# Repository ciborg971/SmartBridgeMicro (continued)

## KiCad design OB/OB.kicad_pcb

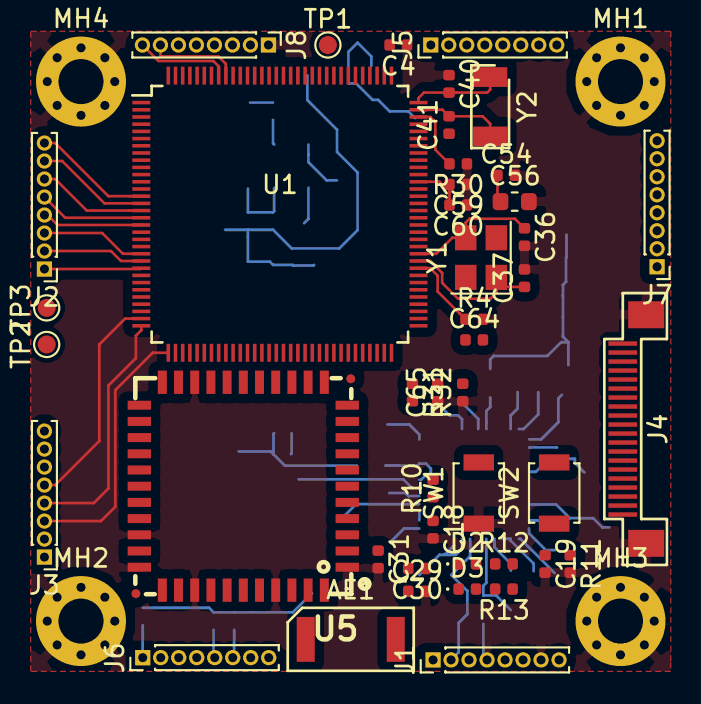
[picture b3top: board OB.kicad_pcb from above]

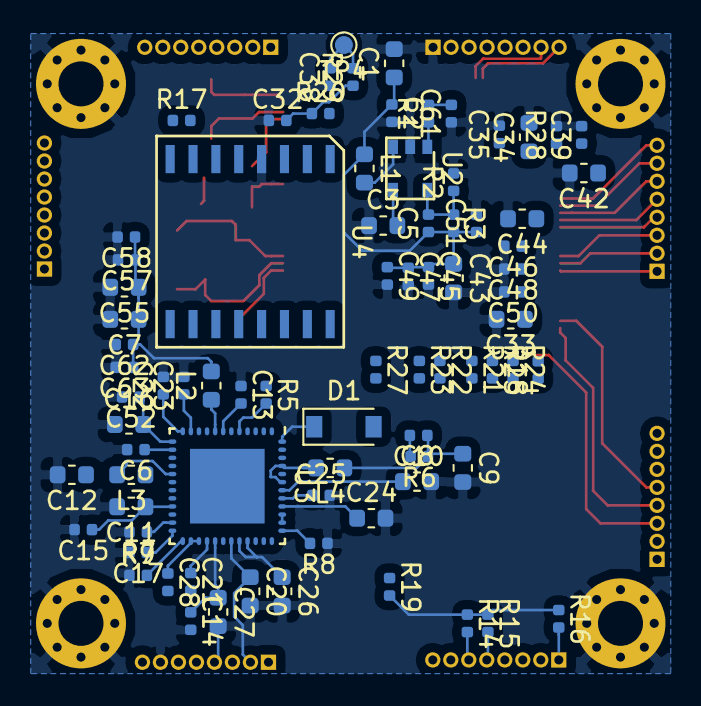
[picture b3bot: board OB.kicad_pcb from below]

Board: 2 copper layers, 128 parts (80 on the bottom side), 126 nets.

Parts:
AE1: 2.4Ant; SOIC-2
C1, C3, C7, C8, C9, C11, C12, C16, C20, C24, C26, C27, C33, C34, C42, C43, C44, C55, C56: 10uF; C_0603_1608Metric
C2, C15, C32: 104; C_0402_1005Metric
C4, C13, C14, C22, C23, C25: 4.7uF; C_0402_1005Metric
C5: 47pF; C_0402_1005Metric
C6: 10uF; C_0402_1005Metric
C10, C17, C21, C28, C29, C30, C31, C35, C38, C45, C46, C47, C52, C57, C58: 1uF; C_0402_1005Metric
C18, C19: 100pF; C_0402_1005Metric
C36, C37: 18pF; C_0402_1005Metric
C39, C48, C49, C50, C51, C54, C59, C60, C61, C62, C63, C64, C65: 104F; C_0402_1005Metric
C40, C41: 20pF; C_0402_1005Metric
D1: 1N4148W-7-F; D_SOD-123
D2, D3: LED; LED_0402_1005Metric
J1: Power; PinHeader_1x08_P1.00mm_Vertical
J2: GPIO_A; PinHeader_1x08_P1.00mm_Vertical
J3: GPIO_B; PinHeader_1x08_P1.00mm_Vertical
J4: CAM; FPC_20
J5: SDC0; PinHeader_1x08_P1.00mm_Vertical
J6: GPIO_D; PinHeader_1x08_P1.00mm_Vertical
J7: USB_ETH; PinHeader_1x08_P1.00mm_Vertical
J8: AUDIO; PinHeader_1x08_P1.00mm_Vertical
L1: 2.2uH_1.5A DCR<0.1R; L_0603_1608Metric
L2: 4.7uH DCR<0.1R 1.1A; L_0603_1608Metric
L3: 4.7uH DCR < 0.1 1.1A; L_0603_1608Metric
L4: 4.7uH DCR < 0.1R 1.1A; L_0603_1608Metric
MH1, MH2, MH3, MH4: MountingHole_Pad; MountingHole_2.5mm_Pad_Via
R1, R18, R19: 100K; R_0402_1005Metric
R2: 100K 1%; R_0402_1005Metric
R3, R7, R28: 200K 1%; R_0402_1005Metric
R4: 240R 1%; R_0402_1005Metric
R5, R17, R27: 10K; R_0402_1005Metric
R6: 30mR; R_0402_1005Metric
R8: 100R; R_0402_1005Metric
R9, R16, R29: 47K; R_0402_1005Metric
R10, R12, R13: 1K; R_0402_1005Metric
R11, R14, R15: 2K; R_0402_1005Metric
R20: 0R; R_0402_1005Metric
R21, R22, R23, R24, R25: 33K; R_0402_1005Metric
R30: 6K 1%; R_0402_1005Metric
R31, R32: 2K 1%; R_0402_1005Metric
SW1, SW2: PWR; SW_SPST_B3U-1000P
TP1: LRADC0; TestPoint_Pad_D1.0mm
TP2: PE1; TestPoint_Pad_D1.0mm
TP3: PE0; TestPoint_Pad_D1.0mm
TP4: Rst; TestPoint_Pad_D1.0mm
U1: V3S; LQFP-128_14x14mm_P0.4mm
U2: SY8088; SOIC-6
U3: AXP203; QFN-48_EP_6.1x6.1_Pitch0.45mm
U4: MX25L12835E; SOIC-16
U5: RTL8723BS(ComboModule); RL-SM02BD(RTL8723BS)
Y1: X1E0000210832; Crystal_SMD_3225-4Pin_3.2x2.5mm
Y2: CC5V-T1A 32.768KHZ +-20PPM 12.5PF; SOIC-2

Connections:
+1V2: C7.1, C55.1, C57.1, C58.1, C62.1, C63.1, L2.2, U1.19, U1.20, U1.21, U1.25, U1.26, U1.38, U1.47, U1.51, U1.56, U1.58, U1.64, U1.80, U1.88, U1.108, U1.126, U3.10
+1V8: C1.1, C2.1, C5.1, C43.1, C45.1, C47.1, C49.1, C51.1, C64.2, L1.1, R3.2, R31.2, U1.59, U1.60, U1.61, U1.62, U1.65, U1.66, U1.67, U1.68, U1.69, U1.70, U1.72, U1.79
+3.3VA: C54.1, C56.1, C61.2, R1.2, U1.76, U1.115
+3V3: C16.2, C24.1, C32.2, C33.1, C44.1, C46.1, C48.1, C50.1, C52.1, C59.2, C60.2, D1.2, J4.8, R5.1, R12.1, R14.1, R15.1, R16.1, R17.1, R18.2, R19.2, R20.1, R21.1, R22.1, R23.1, R24.1, R25.1, R27.1, R29.1, U1.50, U1.57, U1.85, U1.93, U1.104, U1.109, U1.122, U1.127, U3.13, U3.40, U4.2, U4.8, U5.9
+BATT: C8.1, C10.2, J1.6, J4.10, R6.2, U3.38, U3.39, U3.42
/All V3s input output/CSI-PWDN: J4.2, U1.13
/All V3s input output/CSI-RESET: J4.1, U1.11
/All V3s input output/CSI-SCK: J4.5, U1.9
/All V3s input output/CSI-SDA: J4.6, U1.8
/All V3s input output/CSI_1_N: J4.16, U1.82
/All V3s input output/CSI_1_P: J4.15, U1.81
/All V3s input output/CSI_2_N: J4.13, U1.84
/All V3s input output/CSI_2_P: J4.12, U1.83
/All V3s input output/CSI_CLK_N: J4.19, U1.87
/All V3s input output/CSI_CLK_P: J4.18, U1.86
/All V3s input output/CSI_MCLK: J4.3, U1.10
/All V3s input output/EPHY_RX_N: J7.5, U1.89
/All V3s input output/EPHY_RX_P: J7.6, U1.90
/All V3s input output/EPHY_TX_N: J7.7, J7.8, U1.91, U1.92
/All V3s input output/HPCOM: J8.3, U1.125
/All V3s input output/HPCOMFB: J8.2, U1.124
/All V3s input output/MININ1N: J8.4, U1.114
/All V3s input output/MININ1P: J8.5, U1.113
/All V3s input output/SDC1_CLK: U1.5, U5.17
/All V3s input output/SDC1_CMD: R21.2, U1.4, U5.16
/All V3s input output/SDC1_D0: R22.2, U1.3, U5.18
/All V3s input output/SDC1_D1: R23.2, U1.2, U5.19
/All V3s input output/SDC1_D2: R24.2, U1.1, U5.14
/All V3s input output/SDC1_D3: R25.2, U1.128, U5.15
/All V3s input output/SPI_CLK: U1.53, U4.6
/All V3s input output/SPI_CS: R20.2, U1.54, U4.1
/All V3s input output/SPI_HOLD: R17.2, U4.7
/All V3s input output/SPI_MOSI: U1.55, U4.5
/All V3s input output/UART0_RX: J5.7, U1.48
/All V3s input output/UART0_TX: J5.8, U1.49
/All V3s input output/UART2_CTS: U1.42, U5.44
/All V3s input output/UART2_RX: U1.40, U5.42
/All V3s input output/UART2_TX: U1.39, U5.43
/All V3s input output/USB_D_N: J6.7, J7.1, U1.110
/All V3s input output/USB_D_P: J6.8, J7.2, U1.111
/All V3s input output/USB_ID: J6.1, R16.2, U1.100
/All V3s input output/VRA1: C35.1, U1.117
/All V3s input output/VRA2: C34.1, R28.1, U1.118
/PMIC Power Battery/ACIN: C26.1, J1.8, U3.32, U3.33
/PMIC Power Battery/CHGLED: D3.1, U3.36
/PMIC Power Battery/EXTEN: J1.5, U3.20
/PMIC Power Battery/LDO1: C21.1, U3.28
/PMIC Power Battery/LDO2: C22.1, U3.12
/PMIC Power Battery/LDO3: C25.1, U3.41
/PMIC Power Battery/LDO4: C23.1, U3.11
/PMIC Power Battery/N_OE: C19.1, R11.1, SW2.1, U3.4
/PMIC Power Battery/PS: C3.2, C6.1, C11.1, C13.2, C14.1, C15.1, C27.1, J1.3, R13.1, SW2.2, U2.4, U3.7, U3.14, U3.21, U3.29, U3.34, U3.35, U3.44
/PMIC Power Battery/PWRON: C18.1, R10.1, U3.47
/PMIC Power Battery/RECLED: D2.1, U3.18
/PMIC Power Battery/SVREF: C64.1, C65.2, R31.1, R32.2, U1.63, U1.71
/PMIC Power Battery/USBVBUS: C20.1, J1.2, U3.31
/PMIC Power Battery/USB_DRVVBUS: J1.1, U3.6
/PMIC Power Battery/VCC_PE: U1.12, U1.29
/PMIC Power Battery/VCC_RTC: R9.1, U1.98
/PMIC Power Battery/VINT: C28.1, U3.26, U3.27
AP-WAKE-BT: R5.2, U3.5, U5.6
GND: C1.2, C2.2, C3.1, C4.1, C6.2, C7.2, C8.2, C9.2, C11.2, C12.2, C13.1, C14.2, C15.2, C16.1, C17.2, C18.2, C19.2, C20.2, C21.2, C22.2, C23.2, C24.2, C25.2, C26.2, C27.2, C28.2, C29.2, C31.2, C32.1, C33.2, C34.2, C35.2, C36.2, C37.2, C38.1, C39.2, C40.1, C41.1, C42.2, C43.2, C44.2, C45.2, C46.2, C47.2, C48.2, C49.2, C50.2, C51.2, C52.2, C54.2, C55.2, C56.2, C57.2, C58.2, C59.1, C60.1, C61.1, C62.2, C63.2, C65.1, J1.4, J1.7, J4.4, J4.11, J4.14, J4.17, J4.20, J8.1, MH1.1, MH2.1, MH3.1, MH4.1, R2.2, R4.2, R7.2, R8.1, R11.2, R28.2, R30.1, R32.1, SW1.1, U1.116, U2.2, U3.9, U3.16, U3.22, U3.46, U3.49, U4.4, U5.1, U5.20, U5.31, U5.33, U5.36, U5.41, Y1.2, Y1.4
I2C0_CLK: J6.5, R15.2, U1.45, U3.2
I2C0_SDA: J6.6, R14.2, U1.46, U3.1
unnamed: AE1.2, C29.1, C30.2
unnamed: C4.2, U1.97
unnamed: C5.2, R2.1, R3.1, U2.5
unnamed: C9.1, C10.1, L4.1, R6.1
unnamed: C12.1, L3.2, U3.17
unnamed: C17.1, U3.24
unnamed: C30.1, C31.1, U5.2
unnamed: C36.1, U1.75, Y1.3
unnamed: C37.1, U1.74, Y1.1
unnamed: C39.1, C42.1, U1.123
unnamed: C40.2, U1.96, Y2.1
unnamed: C41.2, U1.95, Y2.2
unnamed: D1.1, U3.48
unnamed: D2.2, R12.2
unnamed: D3.2, R13.2
unnamed: J2.1, U1.24
unnamed: J2.2, U1.23
unnamed: J2.3, U1.22
unnamed: J2.4, U1.18
unnamed: J2.5, U1.17
unnamed: J2.6, U1.16
unnamed: J2.7, U1.15
unnamed: J2.8, U1.14
unnamed: J3.1, U1.35
unnamed: J3.2, U1.34
unnamed: J3.3, U1.33
unnamed: J3.4, U1.32
unnamed: J3.5, U1.31
unnamed: J3.6, U1.30
unnamed: J3.7, U1.28
unnamed: J3.8, U1.27
unnamed: J5.1, U1.107
unnamed: J5.2, U1.106
unnamed: J5.3, U1.105
unnamed: J5.4, U1.103
unnamed: J5.5, U1.102
unnamed: J5.6, U1.101
unnamed: J6.2, U1.41
unnamed: J6.3, U1.43
unnamed: J6.4, U1.44
unnamed: J7.3, U1.77
unnamed: J7.4, U1.78
unnamed: J8.6, U1.119
unnamed: J8.7, U1.120
unnamed: J8.8, U1.121
unnamed: L1.2, U2.3
unnamed: L2.1, U3.8
unnamed: L3.1, U3.15
unnamed: L4.2, U3.43, U3.45
unnamed: R1.1, U2.1
unnamed: R4.1, U1.73
unnamed: R7.1, U3.23
unnamed: R8.2, U3.37
unnamed: R10.2, SW1.2
unnamed: R18.1, U5.12
unnamed: R19.1, U5.34
unnamed: R27.2, U5.22
unnamed: R30.2, U1.94
unnamed: TP1.1, U1.112
unnamed: TP2.1, U1.36
unnamed: TP3.1, U1.37
RESET: C38.2, R9.2, R29.2, TP4.1, U1.99, U3.25

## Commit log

2019-02-06 New pmic, global cleanup
2019-02-20 Progress on wifi
2019-02-20 wifi progress on antenna
2019-02-22 wifi antenna done
2019-02-23 SmartBridgeMicro Schematic done
2019-02-23 MicroPilot schematic done
2019-04-14 +esp32picod4 +fix mounting hole position -ceramic antenna +ufl -spi flash
2019-04-14 mounting hole placement fix, routing allmost done
2019-09-22 Power Supply done, audio part fixed, icm + bpm280 added
2019-09-22 Fix commit
2019-09-23 Add i2c connector from V3s, fix sd card detection and remove todos
2019-09-23 Add more footprint, pcb format done, started component placement
2019-09-24 New component placement, progress on rooting
2019-09-26 Change Max13030 and moove ESP32
2019-09-26 ICM rooted
2019-09-28 Camera routed
2019-09-28 Sdcard part routed
2019-09-29 last 4 layers version
2019-09-29 replace 3 ldo by 1, replace icm by mpu and progress on 2 layer
2019-09-29 almost everything is routed !
2019-10-20 SD card connector re routed, only power remaining
2019-10-20 Power part autorouted, replaced micro usb connector by jst sh 5 pin
2019-11-01 progress on pcb cleaning
2019-11-01 cleaner sdcard routing, bom exported (need price and url)
2019-11-01 3 ground issues fixed
2019-11-01 antenna cleanup, ground fixing almost done
2019-11-02 routing done, started filling bom
2019-11-03 length matching done for sdcard, cleaning silkscreen, todo sdio
2019-11-04 progress on fixing esp32 sdio length
2019-11-05 esp32 sdio length matching done
2019-11-05 push to prod ?
2019-11-05 fix adp322, optimize routing
2019-11-05 fix silkscreen
2019-11-06 Apply V3s design guide recommendations
2019-11-16 Move via from pad and rebuild fab files
2019-11-17 increased power track, increased version to 0.2 and re build fab files
2019-11-25 fix d1, d2 package
2019-11-25 fix component packages
2020-06-13 FPGA_ESP32 init : psram + fpga schematic
2020-06-13 FPGA_ESP32 : add header + esp32 with SDIO
2020-06-15 FPGA_ESP32 : add 2 psram ic, rf switch
2020-06-15 FPGA_ESP32 : add spi mux
2020-07-08 FPGA_ESP32 : add camera, change header position
2020-07-10 FPGA_ESP32 : lot of fix + modification
    Replace digital camera by analog camera decoder
    Fix PSRAM io domain 3.3V -> 1.8V
    Start reducing capacitor number
    Add remaining psram pin
    Sheet resize
2020-07-10 FPGA_ESP32 : esp32 enable circuit, flash done, more doc, TODO power !
2020-07-11 FPGA_ESP32 : progress on power and replaced sdio by qspi
2020-07-12 FPGA_ESP32 : power done, antenna matching done, todo crystal and capacitor purge
2020-07-12 FPGA_ESP32 : esp32/rf pa+lna+switch routing progress
